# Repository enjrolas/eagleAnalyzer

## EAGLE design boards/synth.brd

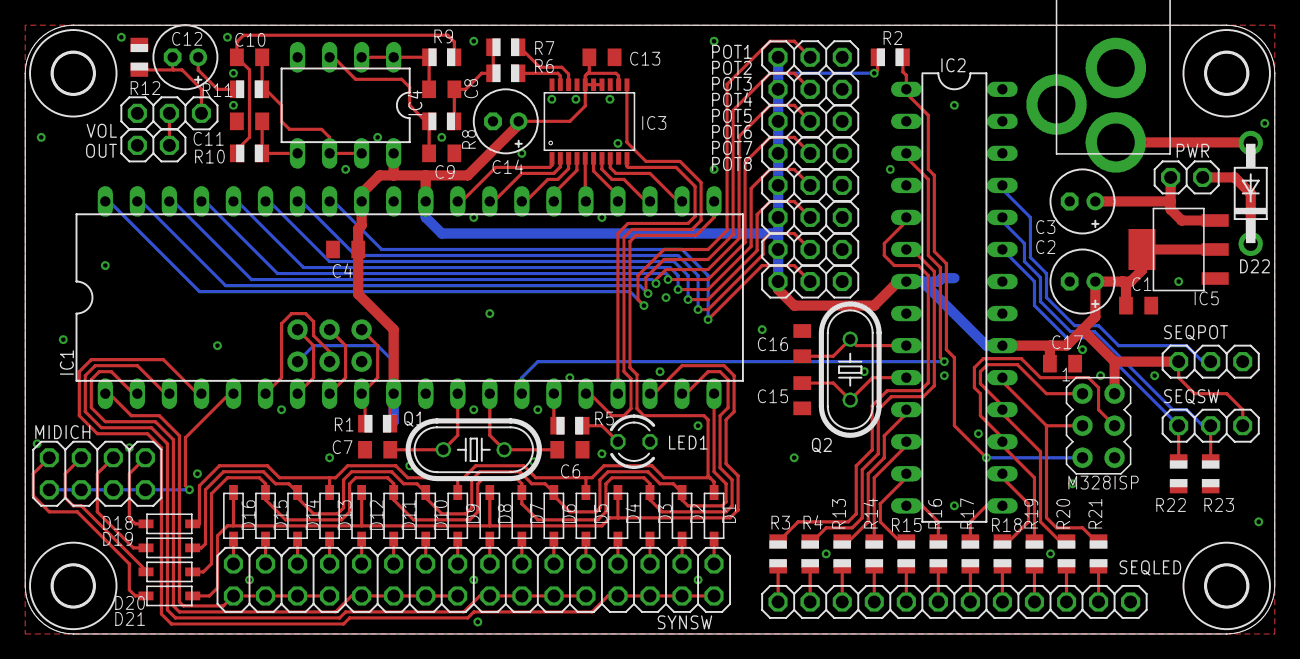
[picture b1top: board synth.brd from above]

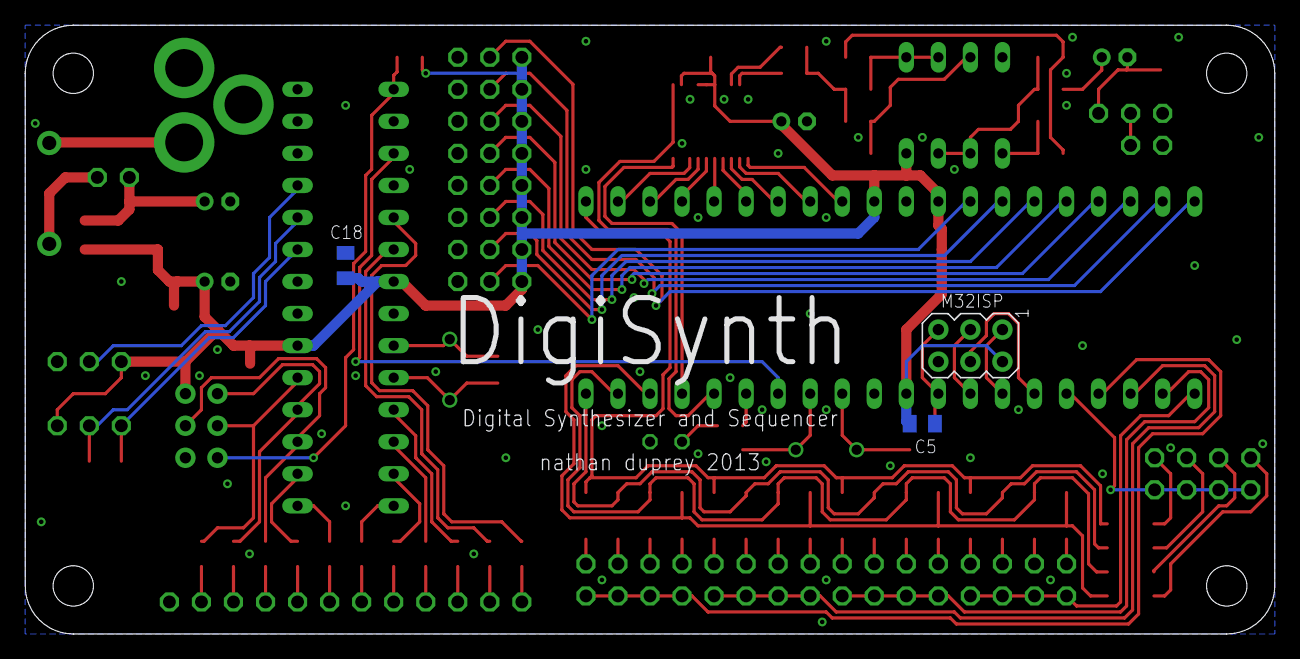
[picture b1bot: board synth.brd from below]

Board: 2 copper layers, 99.1 x 48.3 mm, 93 parts (3 on the bottom side), 100 nets.

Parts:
C1, C4, C5, C13, C17, C18: 0.1uF; C0805K
C2, C14: 10uF; E2-5
C3: 0.33uF; E2-5
C6, C7, C15, C16: 22pF; C0805K
C8: 0.01uF; C0805K
C9, C11: 470pF; C0805K
C10: 0.001uF; C0805K
C12: 4.7uF; E2-5
D1, D2, D3, D4, D5, D6, D7, D8, D9, D10, D11, D12, D13, D14, D15, D16, D18, D19, D20, D21: 1N4148; SOD-123
D22: 1N4001; DO41-7
H1, H2, H3, H4: MOUNT-HOLE3.2; 3,2
IC1: MEGA32-P; DIL40
IC2: ATMEGA168-20P; DIL28-3
IC3: AD7302SMD; TSSOP20
IC4: MCP6002; DIL08
IC5: AP1117E; SOT223-3
LED1: 3MM; LED3MM
M32ISP, M328ISP: AVRISP-6; AVRISP
MIDICH: 2X04
OUT: 1X02
P1: 2.1MMJACKTHM; PJ-102A
POT1, POT2, POT3, POT4, POT5, POT6, POT7, POT8: 1X03
PWR: 1X02
Q1: 16 MHz; HC49U-V
Q2: HC49U-V
R1, R2, R22, R23: 10k; R0805
R3, R4, R5, R13, R14, R15, R16, R17, R18, R19, R20, R21: 220; R0805
R6: 1K; R0805
R7: 274K; R0805
R8: 10.7K; R0805
R9: 4.64K; R0805
R10: 23.7K; R0805
R11: 100; R0805
R12: 1M; R0805
SEQLED: 1X12
SEQPOT: 1X03
SEQSW: 1X03
SYNSW: 2X16
VOL: 1X03

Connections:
GND: C1.2, C2.-, C3.-, C4.2, C5.2, C6.1, C7.1, C9.2, C11.2, C13.2, C14.-, C15.2, C16.2, C17.2, C18.2, IC1.11, IC1.31, IC2.8, IC2.22, IC3.9, IC3.13, IC3.17, IC3.20, IC4.4, IC5.1, LED1.K, M32ISP.6, M328ISP.6, OUT.2, P1.RING, POT1.3, POT2.3, POT3.3, POT4.3, POT5.3, POT6.3, POT7.3, POT8.3, R12.2, R22.1, R23.1, SEQLED.12, SEQPOT.3, VOL.3
unnamed: C7.2, IC1.12, Q1.1
unnamed: C6.2, IC1.13, Q1.2
unnamed: IC1.6, M32ISP.4
unnamed: IC1.8, M32ISP.3
unnamed: IC1.7, M32ISP.1
unnamed: IC1.40, POT1.2
unnamed: IC1.39, POT2.2
unnamed: IC1.9, M32ISP.5, R1.2
unnamed: IC1.38, POT3.2
unnamed: IC1.37, POT4.2
unnamed: IC1.15, R5.1
unnamed: IC1.36, POT5.2
unnamed: LED1.A, R5.2
unnamed: IC1.35, POT6.2
unnamed: IC1.34, POT7.2
unnamed: IC1.33, POT8.2
unnamed: OUT.1, VOL.2
unnamed: D1.A, SYNSW.1
unnamed: IC3.19, R6.2
unnamed: IC2.5, R3.2
unnamed: C12.+, R11.1
unnamed: IC1.5, MIDICH.2, MIDICH.4, MIDICH.6, MIDICH.8
unnamed: C12.-, R12.1, VOL.1
unnamed: D2.A, SYNSW.3
unnamed: D22.A, P1.TIP
unnamed: IC1.3, SYNSW.10, SYNSW.12, SYNSW.14, SYNSW.16
unnamed: C3.+, IC5.3, PWR.2
unnamed: D3.A, SYNSW.5
unnamed: D4.A, SYNSW.7
unnamed: C15.1, IC2.10, Q2.1
unnamed: D5.A, SYNSW.9
unnamed: D6.A, SYNSW.11
unnamed: C16.1, IC2.9, Q2.2
unnamed: IC1.22, IC3.8
unnamed: IC1.23, IC3.7
unnamed: IC1.24, IC3.6
unnamed: IC1.25, IC3.5
unnamed: IC1.26, IC3.4
unnamed: IC1.27, IC3.3
unnamed: IC1.28, IC3.2
unnamed: IC1.29, IC3.1
unnamed: D22.C, PWR.1
unnamed: IC1.17, IC3.10
unnamed: D7.A, SYNSW.13
unnamed: R21.1, SEQLED.11
unnamed: IC2.19, M328ISP.3, R21.2
unnamed: IC1.14, IC2.3
unnamed: IC1.16, IC3.11
unnamed: D8.A, SYNSW.15
unnamed: IC2.18, M328ISP.1, R20.2
unnamed: D9.A, SYNSW.17
unnamed: D10.A, SYNSW.19
unnamed: D11.A, SYNSW.21
unnamed: D12.A, SYNSW.23
unnamed: D13.A, SYNSW.25
unnamed: D14.A, SYNSW.27
unnamed: IC2.1, M328ISP.5, R2.2
unnamed: R3.1, SEQLED.1
unnamed: D18.A, MIDICH.1
unnamed: D15.A, SYNSW.29
unnamed: R4.1, SEQLED.2
unnamed: D1.C, D5.C, D9.C, D13.C, D18.C, IC1.21
unnamed: D19.A, MIDICH.3
unnamed: D16.A, SYNSW.31
unnamed: D20.A, MIDICH.5
unnamed: D21.A, MIDICH.7
unnamed: R13.1, SEQLED.3
unnamed: R14.1, SEQLED.4
unnamed: C8.1, R6.1, R7.1, R8.2
unnamed: IC3.18, R7.2
unnamed: C9.1, IC4.3, R8.1
unnamed: D4.C, D8.C, D12.C, D16.C, D21.C, IC1.18
unnamed: C10.1, R9.1, R10.2
unnamed: C11.1, IC4.5, R10.1
unnamed: C10.2, IC4.6, IC4.7, R11.2
unnamed: R15.1, SEQLED.5
unnamed: C8.2, IC4.1, IC4.2, R9.2
unnamed: R16.1, SEQLED.6
unnamed: R17.1, SEQLED.7
unnamed: R18.1, SEQLED.8
unnamed: R19.1, SEQLED.9
unnamed: R20.1, SEQLED.10
unnamed: IC2.6, R4.2
unnamed: IC2.11, R13.2
unnamed: IC2.12, R14.2
unnamed: IC2.13, R15.2
unnamed: IC2.14, R16.2
unnamed: IC2.15, R17.2
unnamed: IC2.16, R18.2
unnamed: IC2.17, M328ISP.4, R19.2
unnamed: IC2.25, SEQPOT.2
unnamed: IC2.24, R23.2, SEQSW.2
unnamed: IC2.23, R22.2, SEQSW.1
S1: IC1.1, SYNSW.26, SYNSW.28, SYNSW.30, SYNSW.32
S3: IC1.2, SYNSW.18, SYNSW.20, SYNSW.22, SYNSW.24
S7: D3.C, D7.C, D11.C, D15.C, D20.C, IC1.19
S8: IC1.4, SYNSW.2, SYNSW.4, SYNSW.6, SYNSW.8
S10A: D2.C, D6.C, D10.C, D14.C, D19.C, IC1.20
VCC: C1.1, C2.+, C4.1, C5.1, C13.1, C14.+, C17.1, C18.1, IC1.10, IC1.30, IC1.32, IC2.7, IC2.20, IC3.12, IC3.14, IC3.15, IC3.16, IC4.8, IC5.2, IC5.4, M32ISP.2, M328ISP.2, POT1.1, POT2.1, POT3.1, POT4.1, POT5.1, POT6.1, POT7.1, POT8.1, R1.1, R2.1, SEQPOT.1, SEQSW.3

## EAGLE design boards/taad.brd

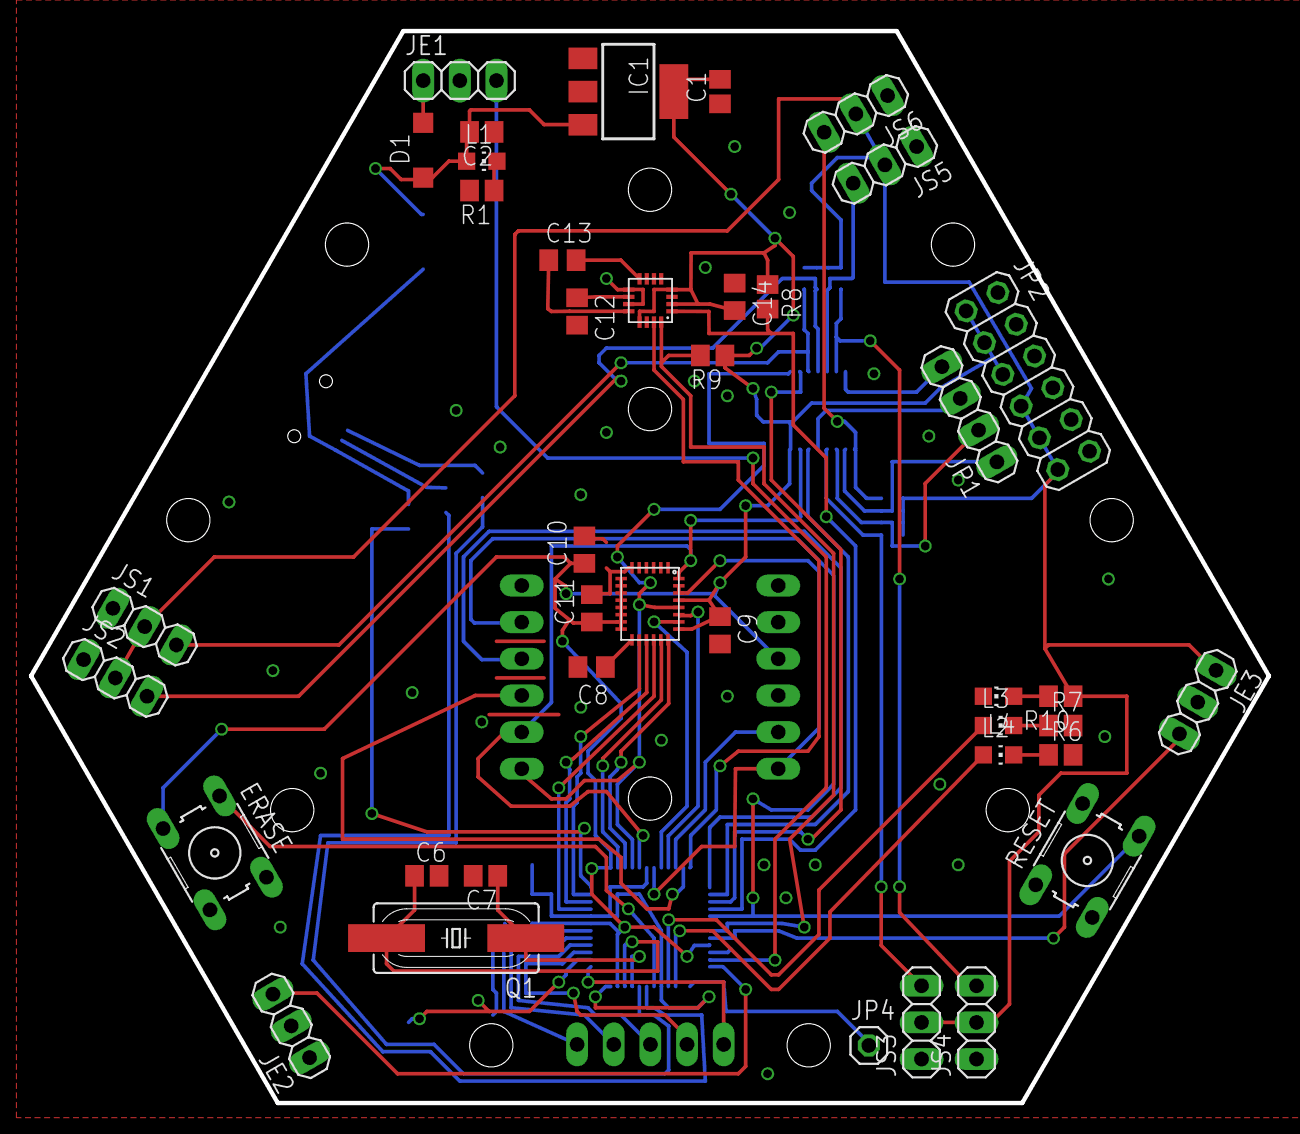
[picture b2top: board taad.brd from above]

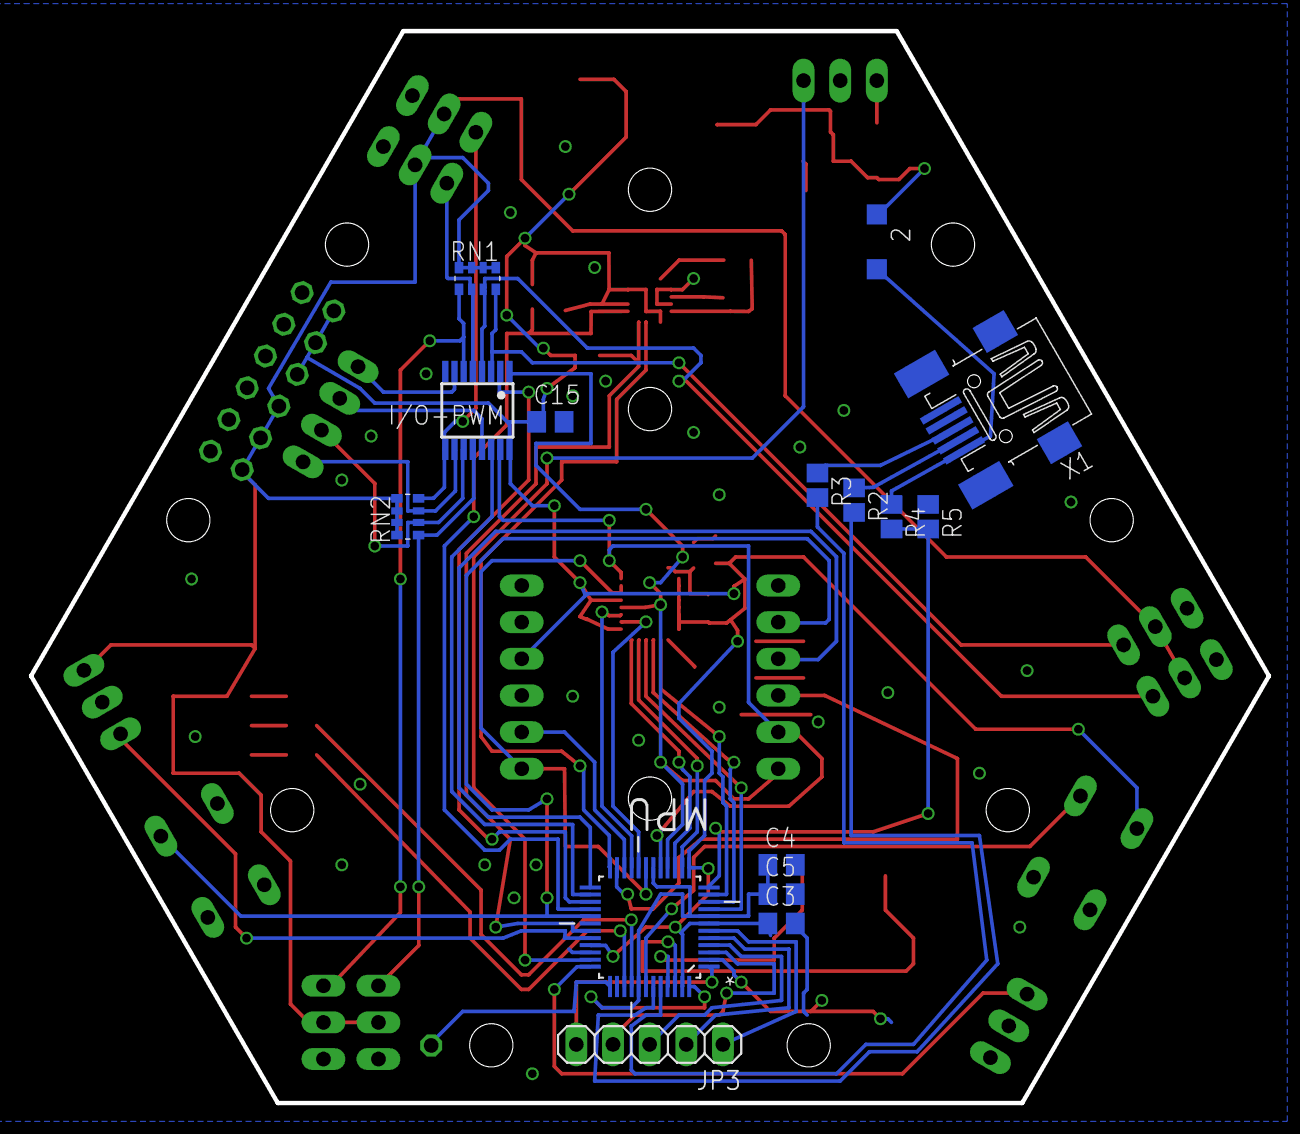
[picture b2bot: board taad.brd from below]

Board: 2 copper layers, 85.8 x 74.3 mm, 56 parts (15 on the bottom side), 63 nets.

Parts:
2: SOD123
C1, C2, C4, C9, C10, C14: 0.1µ; C0805
C3, C11, C15: 10µ; C0805
C5: 2.2µ; C0805
C6, C7: 10p; C0805
C8: 10n; C0805
C12: 4.7µ; C0805
C13: 0.22µ; C0805
COMPASS: HMC5883L; LPCC16
D1: SOD123
ERASE: B3F-10XX
GYRO/ACCEL: LSM330DLC; LGA-28L
I/O-PWM: QSOP16
IC1: LD117AS33TR; SOT223
JE1, JE2, JE3: 1X03
JP1: 1X04
JP2: 2X06
JP3: 1X05
JP4: 1X01
JS1, JS2, JS3, JS4, JS5, JS6: 1X03
L1, L2, L3, L4: CHIP-LED0805
MPU: ATSAM3S2AA-AU; QFP50P900X900X160-48N
Q1: 16 MHz; HC49UP
R1, R6, R7, R10: 160; R0805
R2, R3: 27; R0805
R4: 27k; R0805
R5: 47k; R0805
R8, R9: 2.2k; R0805
RESET: B3F-10XX
RF: MRF24J40MA_TRANSEIVER_MODULE; PIN_HEADERS
RN1, RN2: 2.2k; EXB38V
X1: 32005-201

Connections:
+3V3: C1.2, C3.1, C9.1, C10.1, C11.1, C14.2, C15.1, COMPASS.2, COMPASS.4, COMPASS.13, ERASE.3, GYRO/ACCEL.7, GYRO/ACCEL.8, GYRO/ACCEL.9, GYRO/ACCEL.10, GYRO/ACCEL.11, GYRO/ACCEL.12, GYRO/ACCEL.13, GYRO/ACCEL.14, GYRO/ACCEL.21, GYRO/ACCEL.25, I/O-PWM.16, IC1.4, JP2.1, JP2.3, JP2.5, MPU.7, MPU.13, MPU.33, MPU.47, R8.1, R9.1, RF.10
+5V: JE3.1, JP2.7, JP2.9, JP2.11, JS1.2, JS2.2, JS3.2, JS4.2, JS5.2, JS6.2, R10.1, RN1.5, RN1.6, RN1.7, RN1.8, RN2.5, RN2.6, RN2.7, RN2.8
AD3: JP3.4, MPU.3
AD4: JP3.3, MPU.4
AD5: JP3.2, MPU.5
AD6: JP3.1, MPU.6
ADVREF: JP3.5, MPU.1
COMPASS_DATA_READY: COMPASS.15, MPU.24
DDM: MPU.43, R2.2
DDP: MPU.44, R3.2
DEN_G: GYRO/ACCEL.16, MPU.11
ESC1: JE1.3, MPU.35
ESC2: JE2.3, MPU.36
ESC3: JE3.3, MPU.32
GND: C1.1, C2.1, C3.2, C4.2, C5.2, C6.2, C7.2, C8.2, C9.2, C10.2, C11.2, C12.2, C14.1, C15.2, COMPASS.9, COMPASS.11, GYRO/ACCEL.1, GYRO/ACCEL.2, GYRO/ACCEL.3, GYRO/ACCEL.4, GYRO/ACCEL.5, GYRO/ACCEL.6, I/O-PWM.8, IC1.1, JE1.2, JE2.2, JE3.2, JP2.2, JP2.4, JP2.6, JP2.8, JP2.10, JP2.12, JS1.1, JS2.1, JS3.1, JS4.1, JS5.1, JS6.1, L4.C, MPU.2, MPU.34, R1.2, R5.1, R6.2, R7.2, RESET.2, RF.1, RF.11, RF.12, X1.5
INT1_A: GYRO/ACCEL.20, MPU.15
INT1_G: GYRO/ACCEL.18, MPU.9
INT2_A: GYRO/ACCEL.19, MPU.14
INT2_G: GYRO/ACCEL.17, MPU.10
IO1: I/O-PWM.10, JP1.1, RN2.3
IO2: I/O-PWM.11, JP1.2, RN2.2
IO3: I/O-PWM.13, JP1.3
IO4: I/O-PWM.7, JP1.4
unnamed: D1.A, JE1.1
unnamed: L2.A, MPU.39
unnamed: R3.1, X1.3
unnamed: R2.1, X1.2
unnamed: L1.C, R1.1
unnamed: L3.A, MPU.40
unnamed: L4.A, R10.2
unnamed: L2.C, R6.1
unnamed: L3.C, R7.1
unnamed: ERASE.1, MPU.42
unnamed: JP4.1, MPU.37
unnamed: 2.C, C2.2, D1.C, IC1.3, L1.A
unnamed: C13.2, COMPASS.8
unnamed: C13.1, COMPASS.12
unnamed: C12.1, COMPASS.10
unnamed: C8.1, GYRO/ACCEL.15
NPCS0: GYRO/ACCEL.22, MPU.20
NPCS1: MPU.22, RF.8
NPCS2: GYRO/ACCEL.23, MPU.21
NPCS3: I/O-PWM.2, MPU.27
PWM_CLOCK: I/O-PWM.14, MPU.26
RESET: MPU.29, RESET.4, RF.2
RF_INT: MPU.23, RF.4
RF_WAKE: MPU.25, RF.3
SCK: GYRO/ACCEL.24, I/O-PWM.1, MPU.16, RF.6
SDA: GYRO/ACCEL.28, I/O-PWM.15, MPU.17, RF.5
SDO: GYRO/ACCEL.26, GYRO/ACCEL.27, MPU.19, RF.7
SRV1: I/O-PWM.3, JS1.3, RN1.4
SRV2: I/O-PWM.4, JS2.3, RN1.3
SRV3: I/O-PWM.5, JS5.3, RN1.2
SRV4: I/O-PWM.6, JS4.3, RN1.1
SRV5: I/O-PWM.12, JS3.3, RN2.1
SRV6: I/O-PWM.9, JS6.3, RN2.4
TWI_CLOCK: COMPASS.1, MPU.28, R8.2
TWI_DATA: COMPASS.16, MPU.31, R9.2
USB+5V: 2.A, R4.1, X1.1
USB_CONNECTED: MPU.12, R4.2, R5.2
VDDCORE: C4.1, C5.1, MPU.8, MPU.18, MPU.41, MPU.48
XIN: C6.1, MPU.46, Q1.2
XOUT: C7.1, MPU.45, Q1.1

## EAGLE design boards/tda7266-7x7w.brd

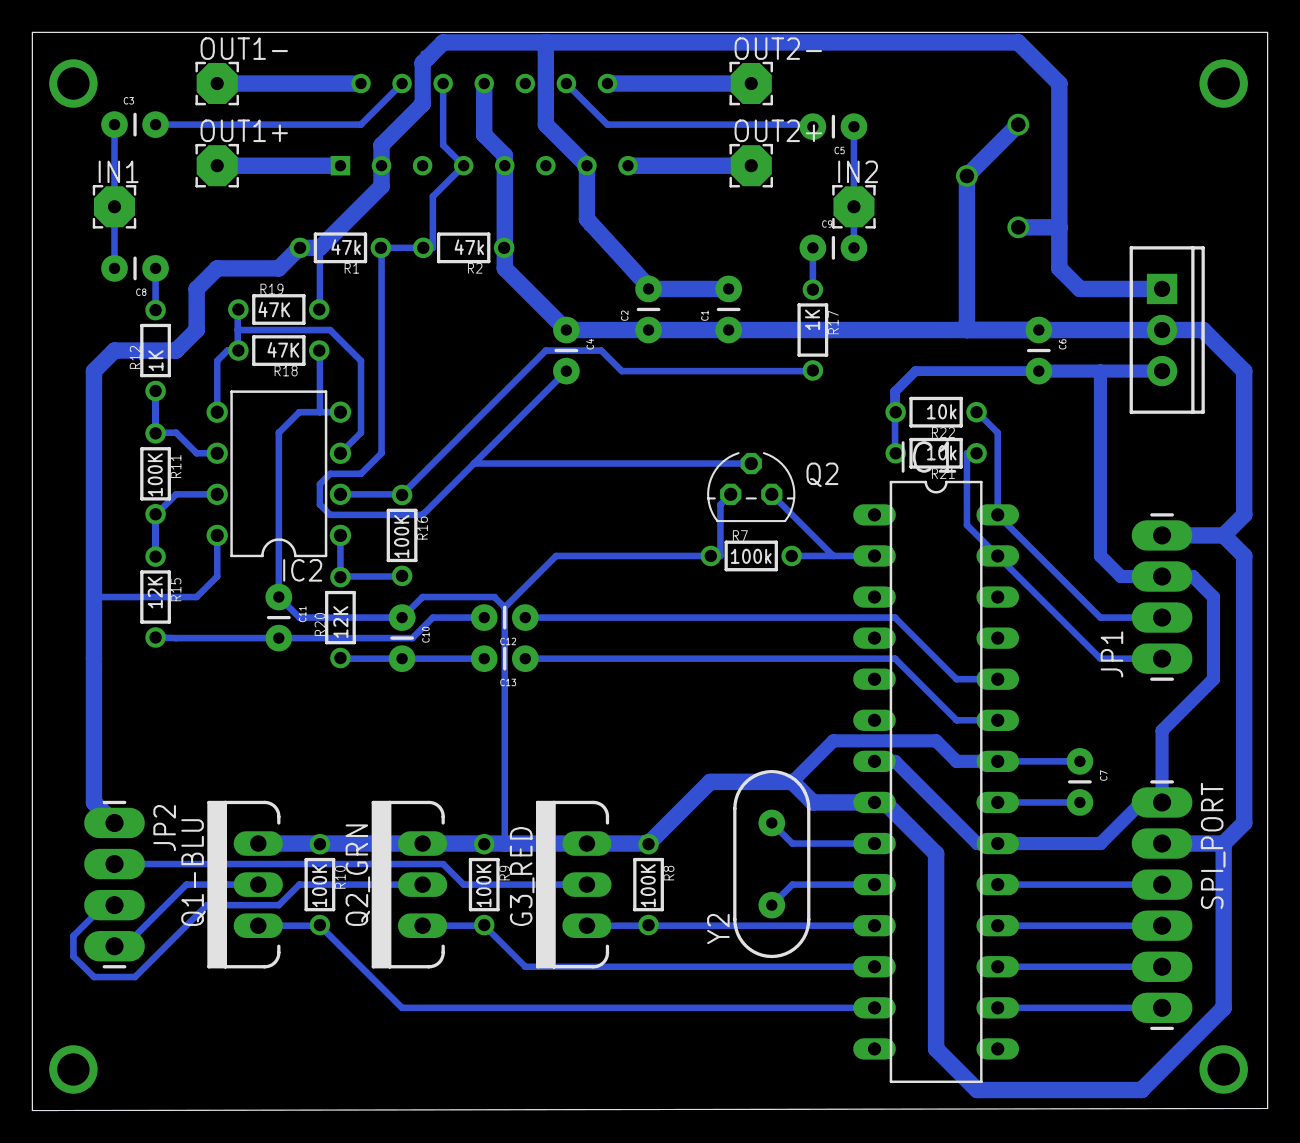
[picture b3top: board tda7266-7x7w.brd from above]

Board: 2 copper layers, 76.4 x 66.7 mm, 47 parts (0 on the bottom side), 39 nets.

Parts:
C1: 470uF; CAP-PTH-SMALL
C2: 100nF; CAP-PTH-SMALL
C3, C5: 22uF; CAP-PTH-SMALL
C4, C6: 10uF; CAP-PTH-SMALL
C7, C8, C9, C12, C13: 1uF; CAP-PTH-SMALL
C10, C11: 4n7; CAP-PTH-SMALL
G3_RED: TO220V
IC1: ATMEGA8-PU; DIL28-3
IC2: LM1458N; DIL08
IN1, IN2: 2,54/0,8
JP1: TWI_HDR; 1X04_LONGPADS
JP2: LED_HDR; 1X04_LONGPADS
OUT1+, OUT1-, OUT2+, OUT2-: 2,54/0,8
Q1-BLU, Q2_GRN: TO220V
Q2: BSS296; TO92
R1, R2: 47k; 1/6W-RES
R7: 100k; 1/6W-RES
R8, R9, R10, R11, R16: 100K; 1/6W-RES
R12, R17: 1K; 1/6W-RES
R15, R20: 12K; 1/6W-RES
R18, R19: 47K; 1/6W-RES
R21, R22: 10k; 1/6W-RES
SPI_PORT: 1X06_LONGPADS
U1: TDA7266; MULTIWATT-15
U2: 7807; TO220-IGO
Y2: HC49US

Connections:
5V: C6.2, IC1.7, IC1.20, JP1.3, R21.2, R22.2, SPI_PORT.1, U2.OUT
/SCK: IC1.19, SPI_PORT.3
/SS: IC1.16, SPI_PORT.6
AUDIO_1: C13.1, IC1.23
AUDIO_2: C12.1, IC1.24
AUD_CTRL: IC1.2, Q2.1, R7.2
BLU: IC1.13, Q1-BLU.1, R10.2
BLU_OUT: JP2.4, Q1-BLU.2
GND: C1.1, C2.1, C4.1, C6.1, C7.1, C10.1, C11.1, G3_RED.3, IC1.8, IC1.22, IC2.4, JP1.4, Q1-BLU.3, Q2.3, Q2_GRN.3, R2.1, R7.1, R8.1, R9.1, R10.1, R18.1, SPI_PORT.2, U1.8, U1.9, U2.GND
GRN: IC1.12, Q2_GRN.1, R9.2
GRN_OUT: JP2.3, Q2_GRN.2
IN1: C3.1, C8.2, IN1.1
IN2: C5.1, C9.2, IN2.1
MISO: IC1.18, SPI_PORT.4
MOSI: IC1.17, SPI_PORT.5
unnamed: IC2.1, R16.2, R20.2
unnamed: IC1.9, Y2.2
unnamed: C8.1, R12.2
unnamed: IC1.10, Y2.1
unnamed: C11.2, C12.2, R15.2
unnamed: C3.2, U1.4
unnamed: C5.2, U1.12
unnamed: C7.2, IC1.21
unnamed: IC2.2, R16.1, R17.2
unnamed: C9.1, R17.1
unnamed: C10.2, C13.2, R20.1
unnamed: IC2.7, R11.2, R15.1
unnamed: IC2.6, R11.1, R12.1
unnamed: C4.2, Q2.2, R1.1, R2.2, U1.6, U1.7
OUT1+: OUT1+.1, U1.1
OUT1-: OUT1-.1, U1.2
OUT2+: OUT2+.1, U1.15
OUT2-: OUT2-.1, U1.14
RED: G3_RED.1, IC1.11, R8.2
RED_OUT: G3_RED.2, JP2.2
SCL: IC1.28, JP1.2, R22.1
SDA: IC1.27, JP1.1, R21.1
VCC: C1.2, C2.2, IC2.8, JP2.1, R1.2, R19.2, U1.3, U1.13, U2.IN
V_DIV: IC2.3, IC2.5, R18.2, R19.1

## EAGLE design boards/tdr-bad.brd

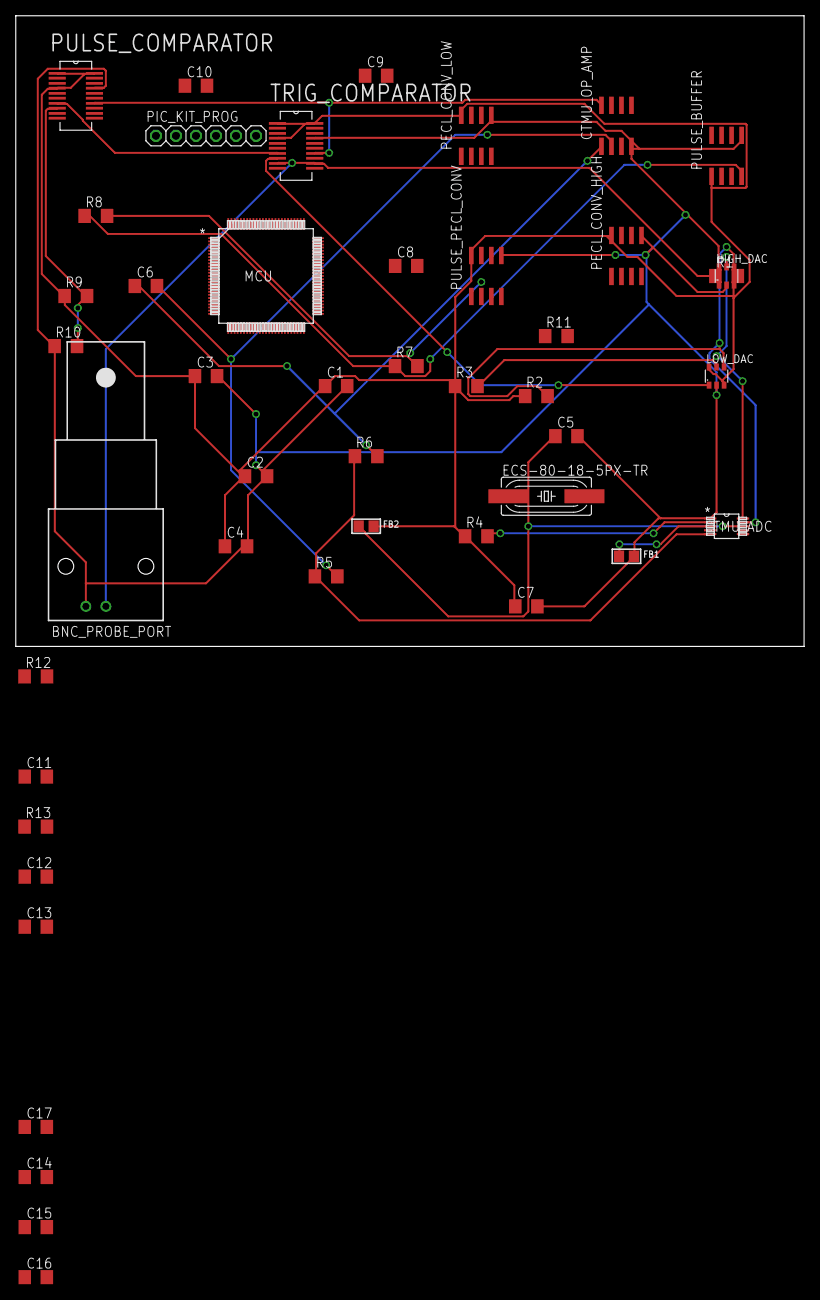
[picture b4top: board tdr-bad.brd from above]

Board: 2 copper layers, 100.0 x 80.0 mm, 46 parts (0 on the bottom side), 40 nets.

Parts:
BNC_PROBE_PORT: 1-227161-6; AMP_227161
C1, C3, C11: .1uF; C1206
C2, C4: 10uF TA; C1206
C5, C6, C7: 1uF; C1206
C8, C9, C10: 27pF; C1206
C12, C13, C14, C15, C16, C17: 10uF; C1206
CTMU_ADC: ADS1115_DGS_10; DGS10
CTMU_OP_AMP: LMC662; SOIC8
ECS-80-18-5PX-TR: 8mhz / 20pf; SM49
FB1, FB2: MMZ2012Y152B; 0805
HIGH_DAC: MCP4725; SOT-23-6
LOW_DAC: MCP4725; SOT-23-6
MCU: PIC24FJXXXDAX10-X/PT; TQFP100_12X12MC
PECL_CONV_HIGH: MC100EPT21; SOIC8
PECL_CONV_LOW: MC100EPT21; SOIC8
PIC_KIT_PROG: 1X06
PULSE_BUFFER: LMH6559; SOIC8
PULSE_COMPARATOR: ADCMP562BRQZ; SOP635P600X175-20N
PULSE_PECL_CONV: MC100EPT21; SOIC8
R1: 50 ohm; R1206
R2, R3, R5: 4.7k; R1206
R4, R9, R10: 10k; R1206
R6, R11, R12, R13: 100 ohm; R1206
R7: 0 ohm (PECL/COMP pulse select); R1206
R8: 0 ohm (MCU pulse select); R1206
TRIG_COMPARATOR: ADCMP562BRQZ; SOP635P600X175-20N

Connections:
+3V3: C1.1, C2.1, C3.1, C4.1, C7.1, C10.1, C12.1, C13.1, FB2.2, HIGH_DAC.3, LOW_DAC.3, LOW_DAC.6, MCU.2, MCU.30, PECL_CONV_HIGH.8, PECL_CONV_LOW.8, PIC_KIT_PROG.2, PULSE_BUFFER.1, PULSE_COMPARATOR.1, PULSE_COMPARATOR.4, PULSE_COMPARATOR.20, PULSE_PECL_CONV.8, R2.1, R3.1, R4.1, R9.1, R13.2, TRIG_COMPARATOR.1, TRIG_COMPARATOR.4, TRIG_COMPARATOR.20
+5V: CTMU_OP_AMP.8, PULSE_COMPARATOR.14, TRIG_COMPARATOR.14
-5V: PULSE_COMPARATOR.7, TRIG_COMPARATOR.7
ADC1: CTMU_ADC.5, R5.1, R6.1
CTMU_EDGE1: MCU.42, PECL_CONV_LOW.7
CTMU_EDGE2: MCU.41, PECL_CONV_HIGH.7
GND: BNC_PROBE_PORT.2, C1.2, C2.2, C3.2, C4.2, C5.2, C7.2, C8.2, C9.2, C10.2, C12.2, C13.2, C16.2, CTMU_ADC.1, CTMU_OP_AMP.4, FB1.2, HIGH_DAC.2, HIGH_DAC.6, LOW_DAC.2, MCU.15, MCU.31, MCU.45, PECL_CONV_HIGH.5, PECL_CONV_LOW.5, PIC_KIT_PROG.5, PULSE_BUFFER.5, PULSE_COMPARATOR.17, PULSE_PECL_CONV.5, R10.1, TRIG_COMPARATOR.17
I2C_SCL: CTMU_ADC.10, HIGH_DAC.5, LOW_DAC.5, MCU.66, R3.2
I2C_SDA: CTMU_ADC.9, HIGH_DAC.4, LOW_DAC.4, MCU.67, R2.2
LOW_DAC_OUT: LOW_DAC.1, TRIG_COMPARATOR.8
MCLR: MCU.13, R12.2
MCU_PULSE_OUT: MCU.49, R8.2
unnamed: PULSE_BUFFER.4, R7.1, R8.1
unnamed: CTMU_ADC.2, R4.2
unnamed: CTMU_ADC.3, FB1.1
unnamed: C5.1, CTMU_ADC.8, FB2.1
unnamed: CTMU_OP_AMP.3, MCU.21
unnamed: C6.1, CTMU_OP_AMP.1, R6.2
unnamed: C6.2, CTMU_OP_AMP.2, R5.2
unnamed: PULSE_COMPARATOR.8, R9.2, R10.2
unnamed: PECL_CONV_LOW.3, TRIG_COMPARATOR.3
unnamed: PECL_CONV_LOW.2, TRIG_COMPARATOR.2
unnamed: PULSE_PECL_CONV.7, R7.2
unnamed: PULSE_BUFFER.8, R1.2
unnamed: C9.1, ECS-80-18-5PX-TR.2, MCU.64
unnamed: C8.1, ECS-80-18-5PX-TR.1, MCU.63
unnamed: PIC_KIT_PROG.1, R11.2
PULSE_OUT_FOR_COMP: MCU.50, PULSE_COMPARATOR.9
TARGET_CLOCK: MCU.26, PIC_KIT_PROG.4
TARGET_DATA: MCU.27, PIC_KIT_PROG.3
TARGET_MCLR: C11.1, R11.1, R12.1, R13.1
TRIGGER: BNC_PROBE_PORT.1, R1.1, TRIG_COMPARATOR.9, TRIG_COMPARATOR.12
T_COMP_OUTB1: PECL_CONV_HIGH.2, TRIG_COMPARATOR.19
T_COMP_OUTB2: PECL_CONV_HIGH.3, TRIG_COMPARATOR.18
VDD: C14.1, MCU.62
VDD_3: C16.1, C17.1, MCU.16, MCU.37
VDD_5: C15.1, MCU.46
VSS: C14.2, MCU.75
VSS_3: C17.2, MCU.36
VSS_5: C15.2, MCU.65

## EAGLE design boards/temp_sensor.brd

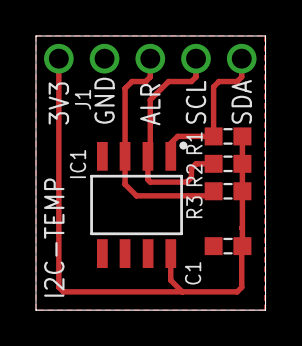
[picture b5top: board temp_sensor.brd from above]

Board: 2 copper layers, 12.8 x 15.2 mm, 6 parts (0 on the bottom side), 5 nets.

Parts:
C1: 0.1uF; CAPC0603
IC1: SOIC127P600X175-8N
J1: PHSP254P1270X254X1154-5S
R1, R2, R3: 10k; RESC0603

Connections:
+3V3: C1.1, IC1.8, J1.1, R1.P$2, R2.P$2, R3.P$2
ALERT: IC1.3, J1.3, R3.P$1
GND: C1.2, IC1.4, IC1.5, IC1.6, IC1.7, J1.2
SCLK: IC1.2, J1.4, R2.P$1
SDA: IC1.1, J1.5, R1.P$1

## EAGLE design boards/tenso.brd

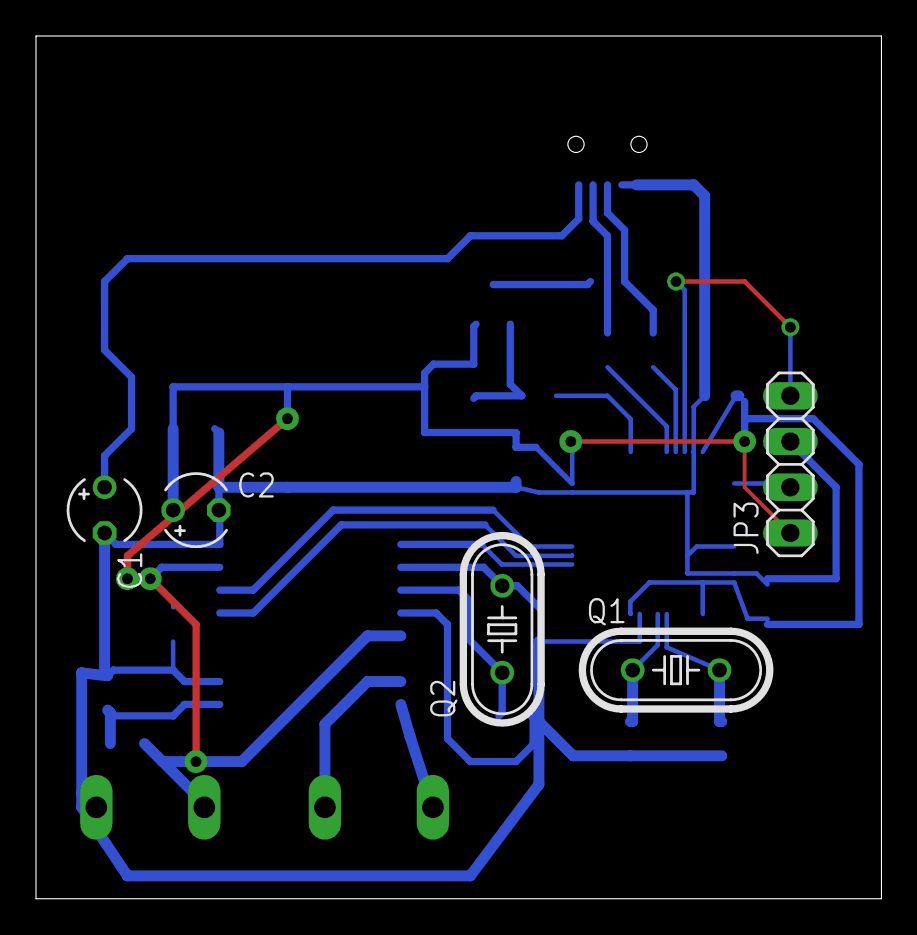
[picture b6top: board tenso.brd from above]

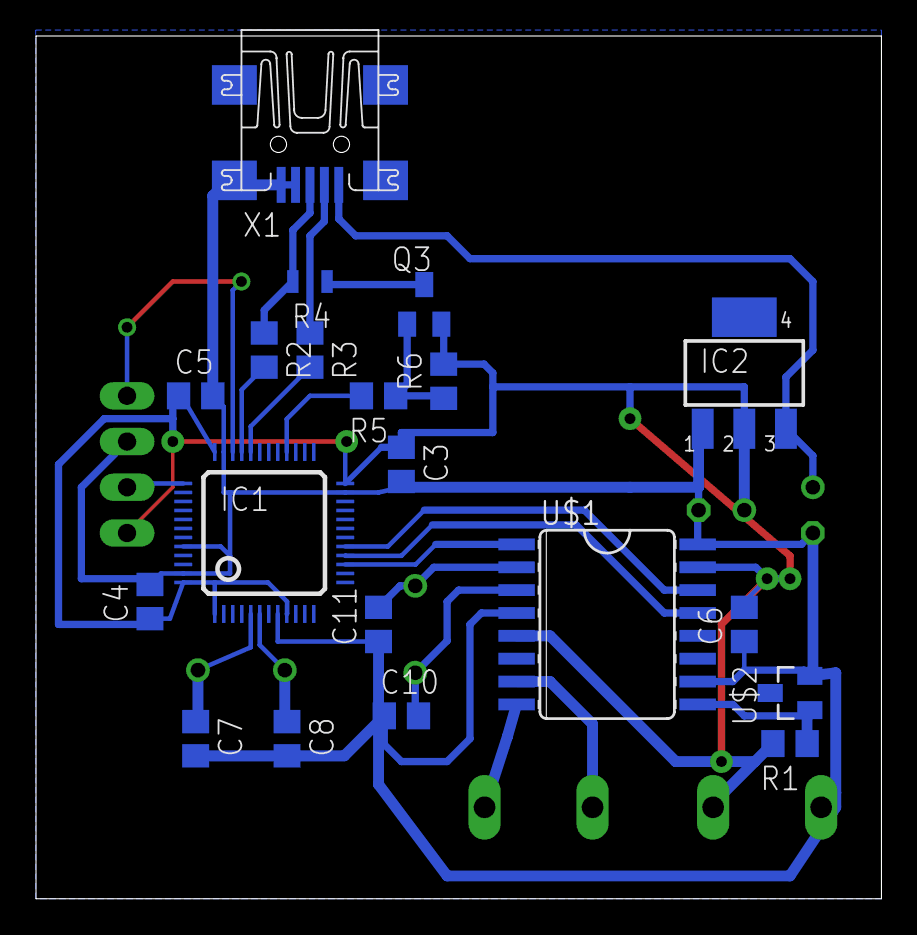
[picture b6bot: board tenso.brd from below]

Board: 2 copper layers, 47.0 x 47.9 mm, 27 parts (20 on the bottom side), 22 nets.

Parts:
C1, C2: 4u7; TT2D4
C3, C4, C5, C6: 100n; C0805
C7, C8, C10, C11: 22p; C0805
IC1: STM32F10XCXT6; TQFP48
IC2: LM33; SOT223
JP1: AIN; 301X2
JP2: APW; 301X2
JP3: SWD; 1X04
Q1: 8M; HC49/S
Q2: 4M; HC49/S
Q3: BCX71SMD; SOT23
R1: 33k; R0805
R2, R3: 22; R0805
R4: 1k5; C0805
R5: 1k; R0805
R6: 10k; R0805
U$1: AD7705R-16; AD7705RNC
U$2: AD1580; SOT23
X1: MINI-USB-UX60-MB-5ST; UX60-MB-5ST

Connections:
+3V3: C2.+, C3.1, C4.1, C5.1, C6.2, IC1.1, IC1.9, IC1.24, IC1.36, IC1.48, IC2.2, JP2.P$2, JP3.1, Q3.2, R1.2, R6.2, U$1.5, U$1.15
+5V: C1.+, IC2.3, X1.1
AIN+: JP1.P$2, U$1.7
AIN-: JP1.P$1, U$1.8
DI: IC1.17, U$1.14
DO: IC1.16, U$1.13
GND: C1.-, C2.-, C3.2, C4.2, C5.2, C6.1, C7.2, C8.2, C10.1, C11.1, IC1.8, IC1.23, IC1.35, IC1.44, IC1.47, IC2.1, JP2.P$1, JP3.3, U$1.4, U$1.10, U$1.16, U$2.2, X1.4, X1.5
unnamed: C7.1, IC1.5, Q1.2
unnamed: C8.1, IC1.6, Q1.1
unnamed: C11.2, Q2.2, U$1.2
unnamed: C10.2, Q2.1, U$1.3
unnamed: R1.1, U$1.9, U$2.1
unnamed: R2.1, R4.2, X1.3
unnamed: R3.1, X1.2
unnamed: Q3.3, R4.1
unnamed: Q3.1, R5.1, R6.1
SCK: IC1.15, U$1.1
SWCLK: IC1.37, JP3.2
SWDIO: IC1.34, JP3.4
USB_DM: IC1.32, R3.2
USB_DP: IC1.33, R2.2
USB_EN: IC1.28, R5.2

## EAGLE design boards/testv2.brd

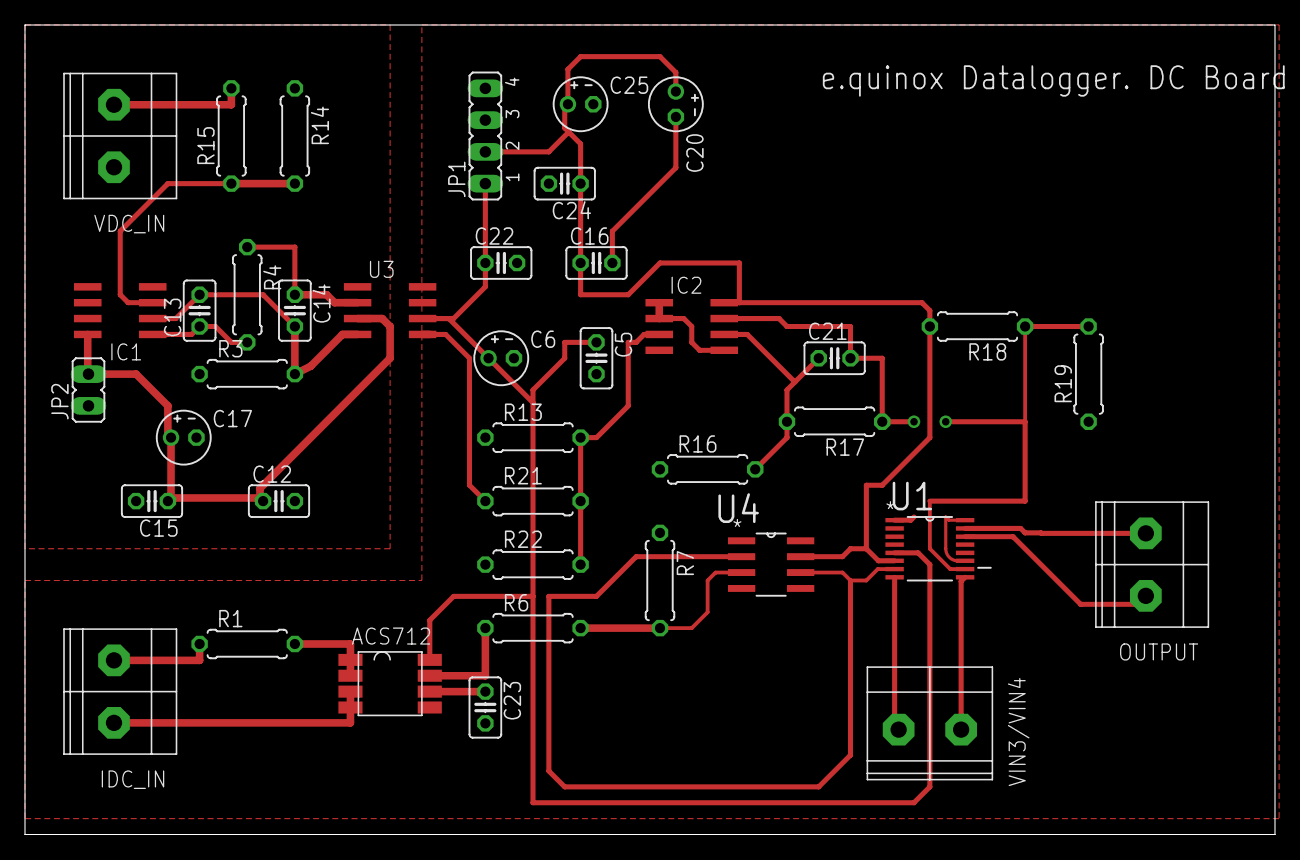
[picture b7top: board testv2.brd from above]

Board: 2 copper layers, 100.0 x 64.8 mm, 40 parts (0 on the bottom side), 27 nets.

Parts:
C5, C12, C13, C14, C15, C16, C21, C22, C23, C24: C025-025X050
C6, C17, C20, C25: E2-4
IC1, IC2: MCP602SN; SO08
IDC_IN: CTB1500/2; CTB1500-2
JP1: JP4
JP2: JP1
OUTPUT: CTB1500/2; CTB1500-2
R1, R3, R4, R6, R7, R13, R14, R15, R16, R17, R18, R19, R21, R22: 0207/7
U1: AD7993BRUZ-0; SOP65P640X120-16N
U3: IL300; SO8
U4: MCP601-E/SN; SOIC127P600X175-8N
U$10: ACS712; SOIC8
VDC_IN: CTB1500/2; CTB1500-2
VIN3/VIN4: CTB1500/2; CTB1500-2

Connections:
+3V3: C16.1, C20.+, C24.1, C25.+, IC2.8, JP1.2, R18.2, U1.6, U4.7
+5V: C5.1, C6.+, C22.1, JP1.1, U1.5, U3.6, U$10.8
+5V/1: C12.1, C15.1, C17.+, IC1.8, JP2.2, U3.3
DC_SENSE: R15.2, VDC_IN.P$2
GND: C5.2, C6.-, C22.2, C23.2, C24.2, C25.-, IC2.4, JP1.3, R7.1, R13.1, R16.1, R19.1, R22.1, U1.1, U1.2, U1.3, U1.4, U1.11, U1.16, U4.4, U$10.5
GND1: C12.2, C15.2, C17.-, IC1.4, IC1.5, IC1.6, JP2.1, R3.1, R14.1, U3.1, VDC_IN.P$1
GND2: C16.2, C20.-
IDC_OUT: U1.7, U4.2, U4.6
unnamed: U1.9, VIN3/VIN4.P$1
unnamed: U1.8, VIN3/VIN4.P$2
unnamed: IDC_IN.P$2, R1.1
unnamed: C13.2, C14.2, IC1.2, R3.2, U3.4
unnamed: C14.1, R4.1, U3.2
unnamed: R1.2, U$10.1, U$10.2
unnamed: C13.1, IC1.1, R4.2
unnamed: IC2.3, R13.2, R21.2, R22.2
unnamed: R21.1, U3.5
unnamed: IC2.1, IC2.2, IC2.5
unnamed: C21.1, IC2.6, R16.2, R17.2
unnamed: IC1.3, R14.2, R15.1
unnamed: IDC_IN.P$1, U$10.3, U$10.4
unnamed: R6.1, U$10.7
unnamed: C23.1, U$10.6
unnamed: R6.2, R7.2, U4.3
unnamed: OUTPUT.P$1, U1.14
SCL: OUTPUT.P$2, U1.15
VDC_OUT: C21.2, IC2.7, R17.1, R18.1, R19.2, U1.10

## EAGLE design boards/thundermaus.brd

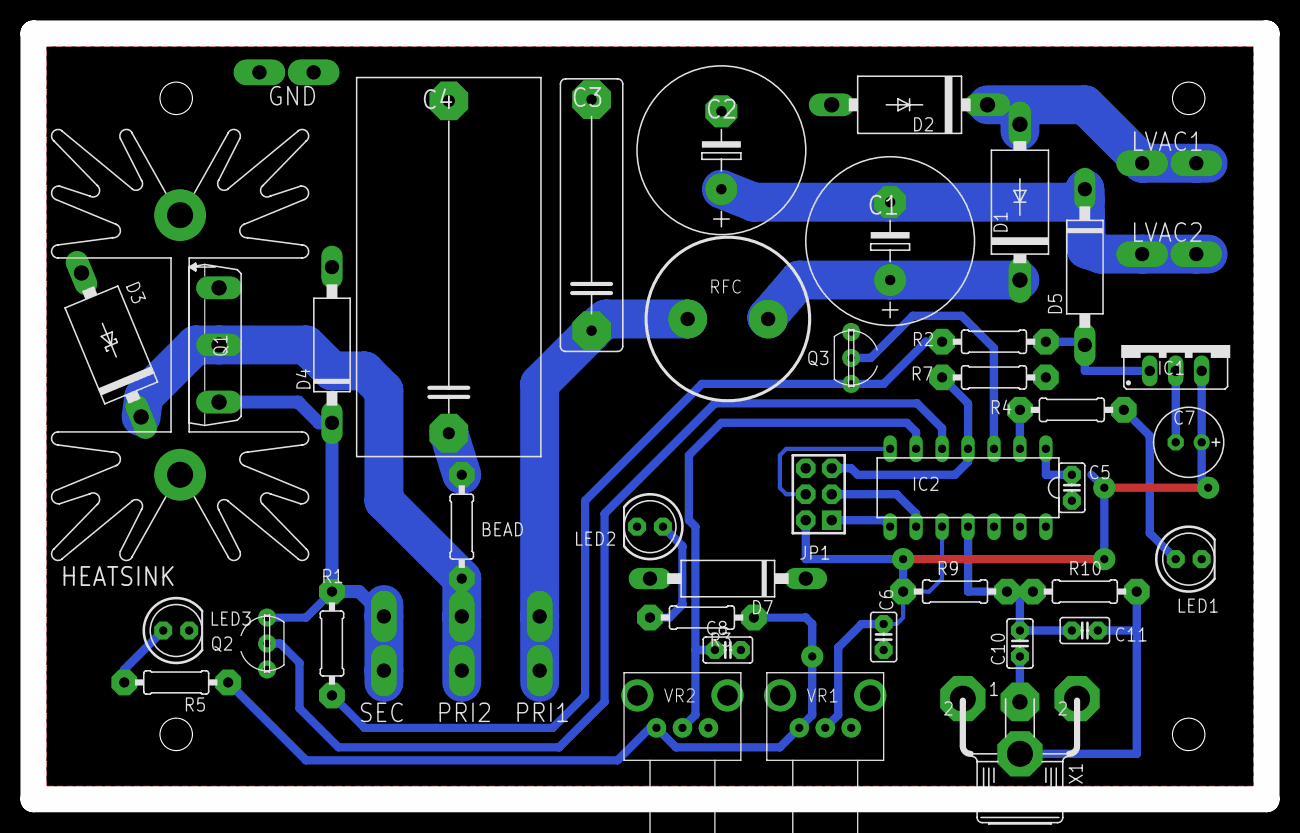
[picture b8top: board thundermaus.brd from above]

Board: 2 copper layers, 120.6 x 74.9 mm, 45 parts (0 on the bottom side), 25 nets.

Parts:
BEAD: 28B0500-100; 0207/10
C1, C2: 2200u, 50v; E7,5-16
C3: 1u; C225-062X268
C4: 715P473512MD3; C325-182X374
C5, C6, C8: 0.1u; C025-025X050
C7: 220u, 16V; E2,5-7
C10: 1u; C025-025X050
C11: 100p; C025-025X050
D1, D2: 1N5401; DO201-15
D3: 1.5KE350; DO201T15
D4, D5, D7: 1N5353; C1702-15
GND: Keystone 1289; F061.060
HEATSINK: 657-15ABP; SK129
IC1: LM7805; 78XXS
IC2: TINY24/44/84-PU; DIL14
JP1: AVR-ISP-6VERT; AVR-ISP-6
LED1, LED2, LED3: LED5MM
LVAC1, LVAC2: Keystone 1289; F061.060
PRI1, PRI2: Keystone 1289; F061.060
Q1: FGH20N60SFD; TO247BV
Q2, Q3: 2n7000; TO237-SW
R1: 1k; 0207/10
R2: 4.7k; 0207/10
R3, R4, R5: 470.; 0207/10
R7: 10k; 0207/10
R9, R10: 100k; 0207/10
RFC: LVP1620-250KL; TJ4-U1
SEC: Keystone 1289; F061.060
VR1, VR2: PTV09
X1: TOBU3

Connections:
5V: C5.1, C7.+, D7.C, IC1.OUT, IC2.1, JP1.2, R3.1, R5.1, R7.1, R9.2, VR1.P1, VR2.P1
16V: D5.A, IC1.IN, R2.2
70VDC: C1.+, D1.C, RFC.1
AUDIO: C10.2, C11.1, IC2.11, R9.1, R10.2
AUDIO-IN: C10.1, X1.1
COLLECTOR: BEAD.1, D3.C, HEATSINK.A2,5, HEATSINK.B2,5, PRI2.A1, PRI2.A2, Q1.D
GATE: D4.C, Q1.G, Q2.1, R1.1, SEC.A1, SEC.A2
GND: C2.-, C3.2, C4.2, C5.2, C6.2, C7.-, C8.2, C11.2, D2.A, D3.A, D4.A, D7.A, GND.A1, GND.A2, IC1.GND, IC2.14, JP1.6, LED1.K, LED2.K, LED3.K, Q1.S, Q2.3, Q3.3, R10.1, VR1.P3, VR1.P$4, VR1.P$5, VR2.P3, VR2.P$4, VR2.P$5, X1.2, X1.2@1, X1.2@2
HVDC: C3.1, PRI1.A1, PRI1.A2, RFC.2
LED: IC2.2, R4.1
LED2-P: LED2.A, R3.2
LED3-P: LED3.A, R5.2
LEDP: LED1.A, R4.2
LVAC1: D1.A, D2.C, LVAC1.A1, LVAC1.A2
LVAC2: C1.-, C2.+, D5.C, LVAC2.A1, LVAC2.A2
MISO: IC2.8, JP1.1
MOSI: IC2.7, JP1.4
PA3: C6.1, IC2.10, VR1.P2
PA7: C8.1, IC2.6, VR2.P2
PB1: IC2.3, Q3.2
PB2: IC2.5, Q2.2
PULLUP_DISABLE: Q3.1, R1.2, R2.1
RESONANT: BEAD.2, C4.1
RST: IC2.4, JP1.5, R7.2
SCK: IC2.9, JP1.3

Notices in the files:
parts and their libraries:
SparkFun: Licensing: CC v3.0 Share-Alike You are welcome to use this library for commercial purposes.
microbuilder: This work is placed in the public domain, and may be freely used for commercial and non-commercial work with the following conditions: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
